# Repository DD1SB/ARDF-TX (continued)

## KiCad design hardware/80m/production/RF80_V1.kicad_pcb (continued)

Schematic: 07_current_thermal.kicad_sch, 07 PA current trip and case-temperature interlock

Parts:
C320: 10n; C_0603_1608Metric; MPN CC0603KRX7R9BB103
C321: 1n; C_0603_1608Metric; MPN CC0603JRNPO9BN102
C322, C323: 100n; C_0603_1608Metric; MPN CC0603KRX7R8BB104
R330: 0.05 ohm / 1% / 1W; R_2512_6332Metric; MPN WSL2512R0500FEA
R331, R332: 10; R_0603_1608Metric; MPN RC0603FR-0710RL
R333: 30k; R_0603_1608Metric; MPN RC0603FR-0730KL
R334, R335, R338, R340: 10k; R_0603_1608Metric; MPN RC0603FR-0710KL
R337: 60.4k; R_0603_1608Metric; MPN RC0603FR-0760K4L
R339: 1.3k; R_0603_1608Metric; MPN RC0603FR-071K3L
R348, R349: 0; R_0603_1608Metric; MPN RC0603JR-070RL; not fitted
TH301: 10k NTC / B25-50=3380; R_0603_1608Metric; MPN NCP18XH103F03RB
U313: INA180A1IDBVT; SOT-23-5; MPN INA180A1IDBVT
U314: LM393BIDR; SOIC-8_3.9x4.9mm_P1.27mm; MPN LM393BIDR

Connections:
GND: C321.2, C322.2, C323.2, R334.2, R338.2, R340.2, R348.2, R349.2, TH301.2, U313.2 (GND), U314.4 (V-); also elsewhere on the board
I_PA_FILTER: C321.1, R333.2, R334.1; also elsewhere on the board
I_PA_RAW: R333.1, U313.1
PACK_2S_REF: U314.2 (-); also elsewhere on the board
PA_GUARD_RAW: U314.7; also elsewhere on the board
SENSE_MINUS: C320.2, R332.2, U313.4 (-)
SENSE_PLUS: C320.1, R331.2, U313.3 (+)
TEMP_HOT_REF: R337.2, R338.1; also elsewhere on the board
TEMP_OPEN_REF: R339.2, R340.1, R348.1, U314.5 (+)
TEMP_SENSE: R335.2, R349.1, TH301.1, U314.6 (-); also elsewhere on the board
UV_POR_N: U314.1; also elsewhere on the board
V3V3: C322.1, C323.1, U313.5 (V+), U314.8 (V+); also elsewhere on the board
VPA_ISO: R330.1, R331.1; also elsewhere on the board
VPA_LOAD: R330.2, R332.1; also elsewhere on the board
VREF_TH: R335.1, R337.1, R339.1; also elsewhere on the board
V_PACK_SCALED: U314.3 (+); also elsewhere on the board

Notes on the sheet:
07 PA current trip and case-temperature interlock
Current trip nominal1.251A (20*0.05ohm=1V/A); targetfaultmute<=100us; dividergain0.25V/A;7.5ustau. Temperature window detects hot/short and detached/open sensor; nominalhot ~80C case. Values/thermal contact, comparator tolerance, filtering and trip latency are qualification gates.
M4A-V1: PRODUCTION-INTENT - NOT RELEASED / all physical gates NOT_RUN.

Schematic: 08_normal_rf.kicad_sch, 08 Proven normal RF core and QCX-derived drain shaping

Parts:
C401: 100n; C_0603_1608Metric; MPN CC0603KRX7R8BB104
C402: 1u; C_0805_2012Metric; MPN CC0805KKX7R9BB105
C403: 22u25; C_1210_3225Metric; MPN GRM32ER71E226KE15L
C404: 47u / 25V; CP_Elec_6.3x5.9; MPN 25SVPF47M
Q401, Q405: BSS138BK,215; SOT-23; MPN BSS138BK,215
Q402: IRF610PBF-BE3; Vishay_IRF610_TO220_StandardPTH; MPN IRF610PBF-BE3
Q403: BD140 / ST; ST_BD140_SOT32_StandardPTH; MPN BD140
Q404: DMN2056U-7; SOT-23; MPN DMN2056U-7
R401, R404: 10k; R_0603_1608Metric; MPN RC0603FR-0710KL
R402, R408: 47k; R_0603_1608Metric; MPN RC0603FR-0747KL
R403: 0; R_0603_1608Metric; MPN RC0603JR-070RL
R405: 1k; R_0603_1608Metric; MPN RC0603FR-071KL
R406: 100; R_2512_6332Metric; MPN CRCW2512100RFKEG
R407: 4.7k; R_0603_1608Metric; MPN RC0603FR-074K7L
R409: 100k; R_0603_1608Metric; MPN RC0603FR-07100KL
R410: 4.7; R_2512_6332Metric; MPN CRCW25124R70FKEG
T401: 9T + 9T bifilar / FT-50A-43; FT50A43_Inline_4Terminal; MPN Amidon FT-50A-43 + AWG24 enamel Cu
TP403: VPA_SHAPED; TestPoint_Pad_D1.0mm; MPN PCB pad / no purchased component
U401: LM5134BMF/NOPB; SOT-23-6; MPN LM5134BMF/NOPB

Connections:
CLK_PA: R408.1, U401.6 (IN); also elsewhere on the board
DRAIN_PA: Q402.2 (D), T401.2 (AB), T401.3 (SA)
GATE_DRV: R403.1, U401.3 (OUT)
GATE_PA: Q402.1 (G), R403.2, R404.1
GND: C401.2, C402.2, C404.2, Q402.3 (S), Q404.2 (S), Q405.2 (S), R402.2, R404.2, R407.2, R408.2, R409.2, U401.4 (VSS); also elsewhere on the board
KEY_DRAIN: Q404.3 (D), R406.2
KEY_TAIL: Q405.1 (G); also elsewhere on the board
PA_INB: Q401.3 (D), R401.2, U401.5 (INB)
PA_KEY: Q404.1 (G); also elsewhere on the board
PA_MUTE_MID: Q401.2 (S), Q405.3 (D), R409.1
PA_PERMIT: Q401.1 (G), R402.1; also elsewhere on the board
RF_RAW: T401.4 (SB); also elsewhere on the board
SHAPE_BASE: C403.2, Q403.1 (B), R405.2, R406.1
VDRV: C401.1, C402.1, C404.1, R401.1, R410.2, U401.1 (VDD); also elsewhere on the board
VPA_LOAD: Q403.3 (E), R405.1, R410.1; also elsewhere on the board
VPA_SHAPED: C403.1, Q403.2 (C), R407.1, T401.1 (AA), TP403.1; also elsewhere on the board

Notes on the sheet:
08 Proven normal RF core and QCX-derived drain shaping
RF core adapted from OpenARDF SignalSlinger HW3.5 (MIT); shaper principle from QCX/W6JL. Keep clock running during graceful key tail; INB immediately mutes on fault. This is NOT the VHF AM modulator.
No PA/drain reservoir after shaper. Driver reservoir is upstream. 9+9 series autotransformer: effective voltage step2:1, load~12.5ohm beforefilter. Transformer drawing is coupled coils; center join is external and explicit. All components on this sheet DNP on Fox-only. No watt-to-Fox RF switching.
M4A-V1: PRODUCTION-INTENT - NOT RELEASED / all physical gates NOT_RUN.

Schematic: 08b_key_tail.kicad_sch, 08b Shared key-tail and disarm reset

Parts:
C451: 100n; C_0603_1608Metric; MPN CC0603KRX7R8BB104
D451: BAT54WS-7-F; D_SOD-323; MPN BAT54WS-7-F
Q406: BSS138BK,215; SOT-23; MPN BSS138BK,215
R451: 1k; R_0603_1608Metric; MPN RC0603FR-071KL
R452: 330k; R_0603_1608Metric; MPN RC0603FR-07330KL
R453: 100; R_0603_1608Metric; MPN RC0603FR-07100RL

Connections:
CW_KEY: R451.1; also elsewhere on the board
GND: C451.2, Q406.2 (S), R452.2; also elsewhere on the board
KEY_TAIL_C: C451.1, D451.1 (K), R452.1, R453.1; also elsewhere on the board
KEY_TAIL_RESET_D: Q406.3 (D), R453.2
KEY_TAIL_SRC: D451.2 (A), R451.2
NOT_ARMED: Q406.1 (G); also elsewhere on the board

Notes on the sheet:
08b Shared key-tail and disarm reset
Path permission alone must not startRF during drain-integrator charging. Normal series INB sink needsPA_PERMIT andKEY_TAIL; FoxRFmute also requiresFOX_PERMIT andKEY_TAIL. Tail usesraw CW_KEY; disarm clampsmemorybelowSchmittlow. KEYhighcannotarm; capturedpath+withdrawaltrippreventsRFtransfer.
RCtailtau33ms; actualholddependsdiodedrop/HC14hysteresis. Benchqualify10-80mshold, longerthanthe3-8msRFdecay. ShorterfallcanclipRF; excessiveholdraisesidle/leakage. ARMlow>=20ms clearsmemory. Afterarming wait>=250msbeforefirstkey, thenverifysettleddrain. A fault bypassesgracefuldecay: PApermission/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
M4A-V1: PRODUCTION-INTENT - NOT RELEASED / all physical gates NOT_RUN.

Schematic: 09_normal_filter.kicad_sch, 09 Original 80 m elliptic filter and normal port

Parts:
C410: 470n; C_1206_3216Metric; MPN C3216X7R2A474K160AB
C411, C415: 1000p; C_0805_2012Metric; MPN C0805C102J1GACTU
C412, C416: 100p; C_0805_2012Metric; MPN C0805C101J1GACTU
C413: 1800p; C_0805_2012Metric; MPN C0805C182J1GACTU
C414: 91p; C_0805_2012Metric; MPN C0805C910J1GACTU
J401: NORMAL 50ohm reference; Phoenix_1727010_StandardPTH; MPN 1727010
L410, L411: 2.7 uH / 20T T60-2; T60_2_20T; MPN Micrometals T60-2 + AWG24 Cu
TP414: GND; TestPoint_Pad_D1.0mm; MPN PCB pad / no purchased component

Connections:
GND: C411.2, C412.2, C413.2, C415.2, C416.2, J401.2, TP414.1; also elsewhere on the board
LPF_N1: C410.2, C411.1, C412.1, L410.1
LPF_N2: C413.1, C414.1, L410.2, L411.1
RF_NORMAL: C414.2, C415.1, C416.1, J401.1, L411.2
RF_RAW: C410.1; also elsewhere on the board

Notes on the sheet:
09 Original 80 m elliptic filter and normal port
Retain SignalSlinger 80m values/topology: series470nF, two2.7uH, 1100/1800/1100pF,91pF acrosssecondcoil. Split1100pF into1000+100pF for obtainable capacitors. Coil recipe is mandatory; no generic power inductors.
Reference50ohm power: J401, calibrated adapter+dummyload. No antenna gain/ERP conversion on80m. Long antenna matcher remains separate: measured verticalwire+defined counterpoise, L-match/variometer. Normal match START range15-50uH fromDF1FO; exacttap/cap values requireinstalledimpedance. A screwter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
M4A-V1: PRODUCTION-INTENT - NOT RELEASED / all physical gates NOT_RUN.

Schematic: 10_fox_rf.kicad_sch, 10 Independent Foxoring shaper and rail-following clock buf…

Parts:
C501: 1u; C_0805_2012Metric; MPN CC0805KKX7R9BB105
C502: 100n; C_0603_1608Metric; MPN CC0603KRX7R8BB104
D501: BAT54WS-7-F; D_SOD-323; MPN BAT54WS-7-F
Q501: MMBT3906,215; SOT-23; MPN MMBT3906,215
Q502: BSS138BK,215; SOT-23; MPN BSS138BK,215
Q503, Q504: MMBT3904,215; SOT-23; MPN MMBT3904,215
R501: 27; R_2512_6332Metric; MPN RC2512FR-0727RL
R502, R504: 1k; R_0603_1608Metric; MPN RC0603FR-071KL
R503: 1.5k; R_0603_1608Metric; MPN RC0603FR-071K5L
R505, R508, R509: 10k; R_0603_1608Metric; MPN RC0603FR-0710KL
R506: 100k; R_0603_1608Metric; MPN RC0603FR-07100KL
R507: 470; R_0603_1608Metric; MPN RC0603FR-07470RL
TP501: VFOX; TestPoint_Pad_D1.0mm; MPN PCB pad / no purchased component
U501: SN74AC00DR; SOIC-14_3.9x8.7mm_P1.27mm; MPN SN74AC00DR

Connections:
CLK_FOX: R505.1; also elsewhere on the board
FOX_BASE: C501.2, Q501.1 (B), R502.2, R503.1
FOX_CLK: D501.1 (K), Q503.3 (C), R507.2, U501.1, U501.4, U501.9
FOX_CLK_B: D501.2 (A), Q503.1 (B), R505.2, R506.1
FOX_FEED: Q501.2 (E), R501.2, R502.1
FOX_GATE1: U501.3; also elsewhere on the board
FOX_GATE2: U501.6; also elsewhere on the board
FOX_GATE3: U501.8; also elsewhere on the board
FOX_GATE_EN: Q504.3 (C), R509.2, U501.2, U501.5, U501.10
FOX_KEY: Q502.1 (G); also elsewhere on the board
FOX_KEY_D: Q502.3 (D), R503.2
FOX_MUTE: R508.1; also elsewhere on the board
FOX_MUTE_B: Q504.1 (B), R508.2
GND: C502.2, Q502.2 (S), Q503.2 (E), Q504.2 (E), R504.2, R506.2, U501.7 (GND), U501.12, U501.13; also elsewhere on the board
V3V3: R501.1; also elsewhere on the board
VFOX: C501.1, C502.1, Q501.3 (C), R504.1, R507.1, R509.1, TP501.1, U501.14 (VCC)

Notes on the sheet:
10 Independent Foxoring shaper and rail-following clock buffer
TinyFox three-gate mechanism with stronger SN74AC00DR; new rail-following NPN input + QCX-style low-current envelope. No electrical RF connection to RF_RAW/RF_NORMAL. Nominal10mW is calibrated at separate J502, not inferred.
M4A-V1: PRODUCTION-INTENT - NOT RELEASED / all physical gates NOT_RUN.

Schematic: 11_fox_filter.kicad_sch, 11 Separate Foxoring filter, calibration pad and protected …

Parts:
C510: 470n; C_1206_3216Metric; MPN C3216X7R2A474K160AB
C511, C515: 1000p; C_0805_2012Metric; MPN C0805C102J1GACTU
C512, C516: 100p; C_0805_2012Metric; MPN C0805C101J1GACTU
C513: 1800p; C_0805_2012Metric; MPN C0805C182J1GACTU
C514: 91p; C_0805_2012Metric; MPN C0805C910J1GACTU
C517: 10n; C_0603_1608Metric; MPN CC0603KRX7R9BB103
J502: FOX ONLY / compact; JST_XH_B3B_StandardPTH; MPN B3B-XH-A(LF)(SN)
L510, L511: 2.7uH +/-5%; 78F_Axial; MPN 78F2R7J-RC
R510, R511, R512: 22; R_0603_1608Metric; MPN RC0603FR-0722RL
R513, R515: 750; R_0603_1608Metric; MPN RC0603FR-07750RL
R514: 6.8; R_0603_1608Metric; MPN RC0603FR-076R8L
R516: 10k; R_0603_1608Metric; MPN RC0603FR-0710KL
TP513: GND; TestPoint_Pad_D1.0mm; MPN PCB pad / no purchased component

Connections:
FOX_GATE1: R510.1; also elsewhere on the board
FOX_GATE2: R511.1; also elsewhere on the board
FOX_GATE3: R512.1; also elsewhere on the board
FOX_ID: C517.1, J502.3, R516.2; also elsewhere on the board
FOX_LPF1: C510.2, C511.1, C512.1, L510.1
FOX_LPF2: C513.1, C514.1, L510.2, L511.1
FOX_PAD_IN: C514.2, C515.1, C516.1, L511.2, R513.1, R514.1
FOX_SUM: C510.1, R510.2, R511.2, R512.2
GND: C511.2, C512.2, C513.2, C515.2, C516.2, C517.2, J502.2, R513.2, R515.2, TP513.1; also elsewhere on the board
RF_FOX: J502.1, R514.2, R515.1
V3V3: R516.1; also elsewhere on the board

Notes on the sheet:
11 Separate Foxoring filter, calibration pad and protected compact port
J502 reference plane: pin1 RF/pin2 definedreturn; use shorttwistedpair coaxadapter sharedfixture. Compactaccessory: ~30 cmradiator+definedcompactreturn; tune independentloading/couplingcartridge. StartingTinyFoxreference100uH plus1.6-15pF; effectiveC5-15pF mayrequire134-402uH. Exact30cm geometry/ta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
M4A-V1: PRODUCTION-INTENT - NOT RELEASED / all physical gates NOT_RUN.

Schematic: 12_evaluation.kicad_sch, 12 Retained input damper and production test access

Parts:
C350: 100u / 35V; CP_Radial_D8.0mm_P3.50mm; MPN EEUFR1V101
C405: 100n / 50V; C_0805_2012Metric; MPN GRM21BR71H104KA01L
R350: 1.5 ohm / 1W; R_2512_6332Metric; MPN CRCW25121R50FKEG
TP703: VPA; Probe_Pad_0p8; MPN PCB copper
TP706: VDRV; Probe_Pad_0p8; MPN PCB copper
TP716: ARMED; Probe_Pad_0p8; MPN PCB copper
TP717: RESET_N; Probe_Pad_0p8; MPN PCB copper
TP721: LEASE_OK; Probe_Pad_0p8; MPN PCB copper
TP723: PA_GUARD_RAW; Probe_Pad_0p8; MPN PCB copper

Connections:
ARMED: TP716.1; also elsewhere on the board
GND: C350.2, C405.2; also elsewhere on the board
LEASE_OK: TP721.1; also elsewhere on the board
PA_GUARD_RAW: TP723.1; also elsewhere on the board
RESET_N: TP717.1; also elsewhere on the board
VDRV: TP706.1; also elsewhere on the board
VIN_PA: C350.1, R350.2; also elsewhere on the board
VIN_PACK: R350.1; also elsewhere on the board
VPA: TP703.1; also elsewhere on the board
VPA_SHAPED: C405.1; also elsewhere on the board

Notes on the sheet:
12 Production test access input damper and low-capacitance probe access
M3B-E2: bounded12.0-16.8V protected4S only; first bring-up uses a CURRENT-LIMITED LAB SUPPLY. R350/C350 damp cable L<=10uH; pack sense remains ahead of R350. TVS is NOT an18V clamp. No driver fitted until power-only OV withdrawal test proves VDRV<=12.6V. No physical tests performed.
Population stages are assembly instructions, not bypasses of hardware interlocks. TH301 electrical sensor is remotely bonded to insulated PA case via test pads; do not fit a second NTC in parallel. R403 zero-ohm can be removed to isolate the gate driver during dummy-load tests. Do not inject28V int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
M4A-V1: PRODUCTION-INTENT - NOT RELEASED / all physical gates NOT_RUN.

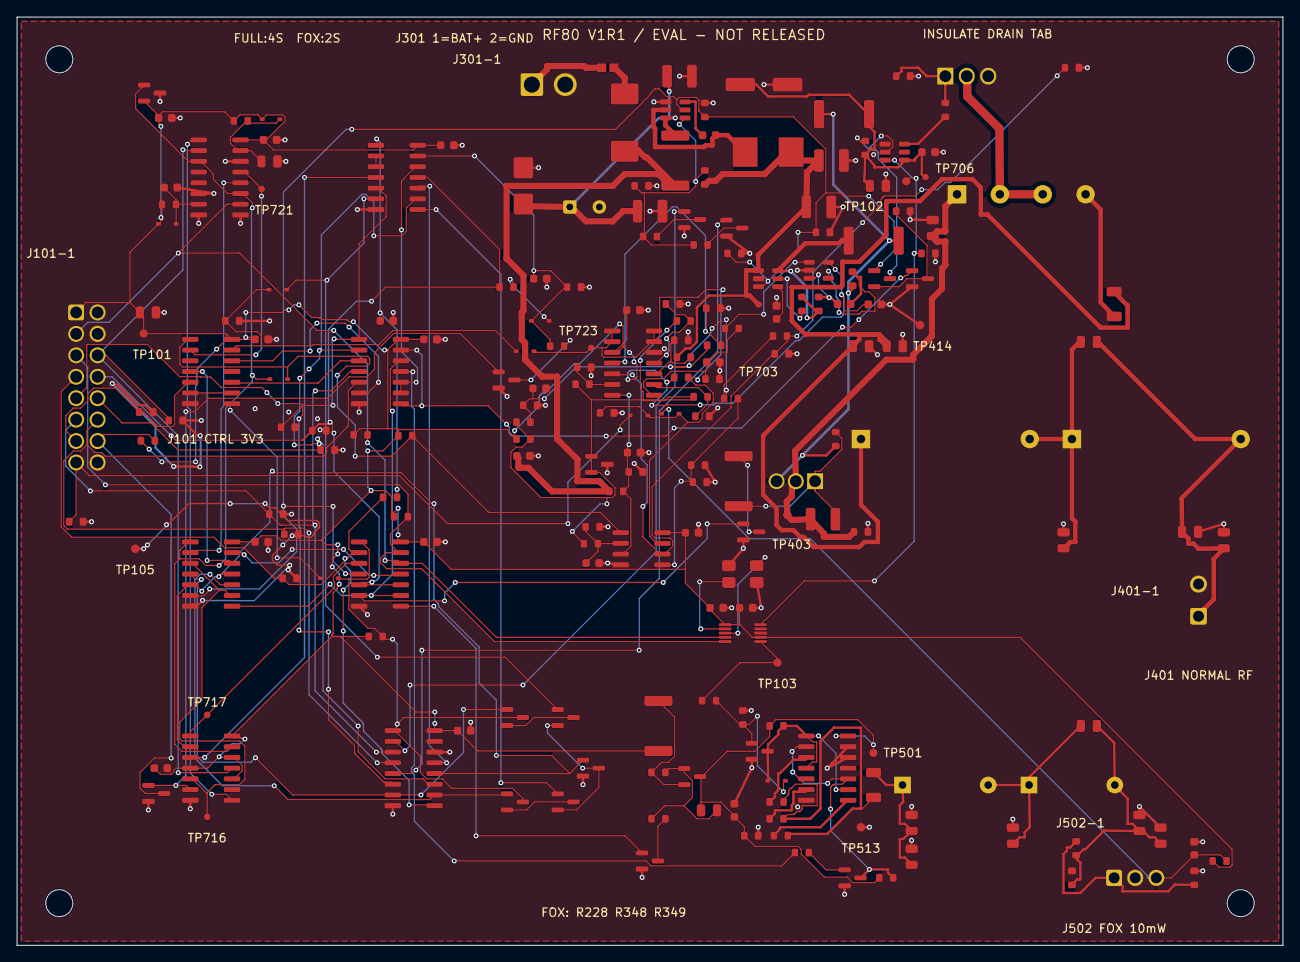
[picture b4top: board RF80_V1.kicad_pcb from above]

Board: 2 copper layers, 150.0 x 110.0 mm, 217 parts (0 on the bottom side), 120 nets.

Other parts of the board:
H1, H2, H3, H4: MountingHole_3.2mm_M3

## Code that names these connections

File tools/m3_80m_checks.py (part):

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    }
    for ref,pinsmap in needed.items():assert parts[ref]['pins']==pinsmap,(ref,parts[ref]['pins'])
    assert parts['Q403']['mpn']=='BD140'
    assert parts['Q401']['pins']=={'1':'PA_PERMIT','2':'PA_MUTE_MID','3':'PA_INB'}
    assert parts['Q405']['pins']=={'1':'KEY_TAIL','2':'GND','3':'PA_MUTE_MID'}
    assert parts['Q406']['pins']=={'1':'NOT_ARMED','2':'GND','3':'KEY_TAIL_RESET_D'}
    assert parts['U203']['pins']['13']=='KEY_TAIL_C' and parts['U203']['pins']['12']=='KEY_TAIL_N'
    assert parts['U212']['pins']['8']=='KEY_TAIL'
    assert parts['U212']['pins']['12']=='FOX_PERMIT' and parts['U212']['pins']['13']=='KEY_TAIL' and parts['U212']['pins']['11']=='FOX_MUTE'
    assert parts['R451']['pins']['1']=='CW_KEY'
    assert parts['U223']['pins']['1']=='RESET_N' and parts['U223']['pins']['2']=='ARM_ACCEPT' and parts['U223']['pins']['3']=='ARM_CLK' and parts['U223']['pins']['4']=='V3V3'
    assert parts['U202']['pins']['6']=='GND' and parts['U202']['pins']['14']=='GND'
    assert parts['D201']['pins']=={'1':'V3V3','2':'LEASE_RC'} and parts['D202']['pins']=={'1':'V3V3','2':'BUS_RC'}
    for ref in ('R451','D451','R452','C451','R453','Q406'):
        assert parts[ref]['population']=='BOTH'
    assert parts['D501']['mpn']=='BAT54WS-7-F'
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    for p in parts.values():
        if p['group']=='fox' or p['ref']=='J502':
            assert not forbidden.intersection(p['pins'].values()),p['ref']
    assert parts['U501']['pins']['14']=='VFOX'
    for pin in ('2','5','10'):assert parts['U501']['pins'][pin]=='FOX_GATE_EN'
    for ref in ('R510','R511','R512'):assert parts[ref]['pins']['2']=='FOX_SUM'
    # Pad and transmission-zero positions are different requirements from generic LPFs.
    assert set(parts['C414']['pins'].values())=={'LPF_N2','RF_NORMAL'}
    assert set(parts['C514']['pins'].values())=={'FOX_LPF2','FOX_PAD_IN'}
    assert parts['R501']['value']=='27'
    assert parts['R501']['footprint']=='Resistor_SMD:R_2512_6332Metric'
    assert parts['Q504']['pins']['3']=='FOX_GATE_EN'

    footprints=0
    for p in parts.values():
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
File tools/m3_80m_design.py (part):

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    s=d.sheet('01_source_interface','01 Controller interface and local source')
    s.text('One local Si5351; no MCU/RTC/UI on RF PCB. Shared 3.3 V stays powered during inhibited I2C setup.\nController wide-input regulator remains a proposal: evaluation fixture supplies bounded 3.3 V separately.',15,22)
    pins={'1':'V3V3','2':'GND','3':'SCL','4':'GND','5':'SDA','6':'LEASE','7':'ARM','8':'CW_KEY','9':'PA_REQ','10':'FOX_REQ','11':'PWR0','12':'PWR1','13':'MUTE_N','14':'FAULT_N','15':'PACK4_OK','16':'GND'}
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    r(s,'R349','0','TEMP_SENSE','GND',110,262,'FOX',note='Unused LM393 half input low in Fox-only; full DNP.')
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
    s=d.sheet('08_normal_rf','08 Proven normal RF core and QCX-derived drain shaping')
    s.text('RF core adapted from OpenARDF SignalSlinger HW3.5 (MIT); shaper principle from QCX/W6JL.\nKeep clock running during graceful key tail; INB immediately mutes on fault. This is NOT the VHF AM modulator.',15,23)
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    r(s,'R401','10k','VDRV','PA_INB',180,65,'NORMAL','normal_driver');fet(s,'Q401','PA_PERMIT','PA_INB','PA_MUTE_MID',245,65,'NORMAL','normal_driver');r(s,'R402','47k','PA_PERMIT','GND',315,65,'NORMAL','normal_driver')
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
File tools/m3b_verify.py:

#!/usr/bin/python3
"""Current PCB/netlist/R1 logic regression, package and artifact consistency."""
import csv,hashlib,json,os,sys
from pathlib import Path
from collections import Counter
import xml.etree.ElementTree as ET
import pcbnew as p
ROOT=Path(__file__).resolve().parents[1];HW=ROOT/'hardware/80m';REVISION=json.loads((HW/'RF80.electrical.json').read_text())['revision'];D=HW/'review'/REVISION;PREFIX='M3B_E2'if REVISION=='M3B-E2'else'M3B'
def main():
 m=json.loads((HW/'RF80.electrical.json').read_text());parts={x['ref']:x for x in m['parts']if not x['ref'].startswith('#')};b=p.LoadBoard(str(HW/'RF80.kicad_pcb'));fp={f.GetReference():f for f in b.GetFootprints()};xml=ET.parse(D/'RF80.xml')
 expected={}
 for n in xml.findall('./nets/net'):
  for nd in n.findall('node'):expected[(nd.attrib['ref'],nd.attrib['pin'])]=n.attrib['name'].removeprefix('/')
 assert set(parts)==set(fp)-{'H1','H2','H3','H4'}
 checked=0
 for r,f in fp.items():
  if r not in parts:continue
  assert str(f.GetFPID().GetLibNickname())+':'+str(f.GetFPID().GetLibItemName())==parts[r]['footprint'],(r,'FPID')
  for d in f.Pads():
   target=expected.get((r,d.GetNumber()),'');assert d.GetNetname()==target,(r,d.GetNumber(),d.GetNetname(),target);checked+=1
 for name in ('DRC','ERC'):
  j=json.loads((D/(name+'.json')).read_text());violations=j.get('violations',[v for s in j.get('sheets',[])for v in s.get('violations',[])]);assert not violations,(name,violations)
  if name=='DRC':assert not j['unconnected_items']and not j['schematic_parity']
 os.environ['RF80_NETLIST']=str(D/'RF80.xml')
 from m3a_r1_logic import verify
 lr=verify();assert lr['truth_cases']==256 and len(lr['state_scenarios'])==31 and len(lr['timing_corners'])==16
 (ROOT/('docs/'+PREFIX+'_LOGIC_RESULTS.json')).write_text(json.dumps(dict(evaluation_revision=REVISION,netlist=str((D/'RF80.xml').relative_to(ROOT)),retained_R1_contract=lr),indent=2)+'\n')
 tracks=[t for t in b.GetTracks()if not isinstance(t,p.PCB_VIA)];vias=[t for t in b.GetTracks()if isinstance(t,p.PCB_VIA)]
 assert all(t.GetWidth()>=p.FromMM(.15)for t in tracks)
 assert all(v.GetDrill()>=p.FromMM(.3)and v.GetWidth(p.F_Cu)>=p.FromMM(.6)for v in vias)
 for v in vias:
  for f in fp.values():
   for d in f.Pads():
    if d.GetAttribute()==p.PAD_ATTRIB_SMD:assert not d.HitTest(v.GetPosition()),('Via in SMD pad',f.GetReference(),d.GetNumber())
 # Independent manufacturer physical-pin maps, not symbol graphic order.
 maker={'U101':{'1':'V3V3','2':'XA','3':'XB','4':'SCL','5':'SDA','6':'CLK_FOX','7':'V3V3','8':'GND','10':'CLK_PA'},'U401':{'1':'VDRV','3':'GATE_DRV','4':'GND','5':'PA_INB','6':'CLK_PA'},'U301':{'1':'GND','2':'SW_PA','3':'VIN_PA','4':'FB_PA','5':'PA_PERMIT','6':'BOOT_PA'},'U302':{'1':'VPA','2':'GND','3':'PA_PERMIT','4':'CT_PA','5':'QOD_PA','6':'VPA_ISO'},'U313':{'1':'I_PA_RAW','2':'GND','3':'SENSE_PLUS','4':'SENSE_MINUS','5':'V3V3'},'Q402':{'1':'GATE_PA','2':'DRAIN_PA','3':'GND'},'Q403':{'1':'SHAPE_BASE','2':'VPA_SHAPED','3':'VPA_LOAD'},'U311':{'1':'VREF_2V5','2':'VREF_2V5','3':'GND'},'U202':{'13':'LEASE_OK','12':'BUS_HOLDOFF_N'},'U224':{'1':'HEALTH_N','9':'ARM'},'U501':{'7':'GND','14':'VFOX','3':'FOX_GATE1','6':'FOX_GATE2','8':'FOX_GATE3'},'J502':{'1':'RF_FOX','2':'GND','3':'FOX_ID'}}
 for ref,pinmap in maker.items():
  for pin,net in pinmap.items():assert expected[(ref,pin)]==net,(ref,pin,net)
 for q in parts.values():
  if q['group']=='fox':assert not set(q['pins'].values())&{'DRAIN_PA','GATE_PA','VPA_SHAPED','RF_NORMAL'}
 assert b.GetCopperLayerCount()==2
 assert all(abs(p.ToMM(q.GetDrillSize().x)-1.3)<.001 for q in fp['Q402'].Pads())
 assert all(abs(p.ToMM(q.GetDrillSize().x)-1.2)<.001 for q in fp['J101'].Pads())
 assert fp['F301'].GetFPID().GetLibItemName()=='Fuse_467_0603'
 assert len(list(b.Zones()))==2
 pads=[(r,f,parts[r])for r,f in fp.items()if r.startswith('TP')]
 with(D/'probe-map.csv').open('w')as out:
  w=csv.writer(out,lineterminator='\n');w.writerow(['reference','net','x_mm_absolute','y_mm_absolute','population','probe_caution'])
  for r,f,q in sorted(pads):w.writerow([r,q['pins']['1'],p.ToMM(f.GetPosition().x),p.ToMM(f.GetPosition().y),q['population'],'DRAIN: rated <=1pF active/differential'if q['pins']['1']=='DRAIN_PA'else 'Reset/clock: <=1pF active; local ground spring'])
 with(D/'population-map.csv').open('w')as out:
  w=csv.writer(out,lineterminator='\n');w.writerow(['reference','value','MPN','footprint','population','full_fit','fox_fit','x_mm_absolute','y_mm_absolute','rotation_deg'])
  for r,f in sorted(fp.items()):
   q=parts.get(r)
   if q:w.writerow([r,q['value'],q['mpn'],q['footprint'],q['population'],q['population']in('BOTH','NORMAL'),q['population']in('BOTH','FOX'),p.ToMM(f.GetPosition().x),p.ToMM(f.GetPosition().y),f.GetOrientationDegrees()])
 nets={}
 for n in ('GATE_DRV','GATE_PA','DRAIN_PA','VDRV','RF_NORMAL','RF_FOX','CLK_PA','CLK_FOX','SW_PA','VPA_ISO','VPA_LOAD'):
  ts=[t for t in tracks if t.GetNetname()==n];nets[n]=dict(track_length_mm=round(sum(p.ToMM(t.GetLength())for t in ts),3),widths_mm=sorted(set(round(p.ToMM(t.GetWidth()),3)for t in ts)),layers=sorted(set(b.GetLayerName(t.GetLayer())for t in ts)))
 models={}
 for f in fp.values():
  for model in f.Models():
   fn=model.m_Filename.replace('${KIPRJMOD}',str(HW)).replace('${KICAD10_3DMODEL_DIR}','/usr/share/kicad/3dmodels');assert Path(fn).exists(),fn;models[f.GetReference()]=model.m_Filename
 report=dict(date=m['date'],revision=REVISION,baseline_commit='55a5b3f',status='CAD AND IDEAL LOGIC CHECKS PASS; ALL PHYSICAL GATES NOT_RUN',manifest_refs=len(m['parts']),electrical_footprints=len(parts),mounting_holes=4,footprints=len(fp),physical_pad_memberships_checked=checked,manufacturer_pinmaps_checked=sorted(maker),test_pads=len(pads),track_segments=len(tracks),through_vias=len(vias),zones=2,board_mm=[210,160,1.6],copper_layers=2,track_width_histogram=dict(sorted(Counter(round(p.ToMM(t.GetWidth()),3)for t in tracks).items())),critical_net_geometry=nets,models_resolve=len(models),ERC_violations=0,DRC_violations=0,unrouted=0,schematic_parity=0,logic_truth_cases=256,state_scenarios=31,timing_corners=16,not_proved=['Physical propagation/reset recovery/metastability','Driver OV withdrawal timing and capacitor hot ESR','Cable/source transient envelope','RF power/efficiency/emissions/CW/thermal/antenna/isolation','Incoming exact component mechanical fit and stock'])
 (ROOT/('docs/'+PREFIX+'_CHECK_RESULTS.json')).write_text(json.dumps(report,indent=2)+'\n')
 print('PASS M3B:',checked,'pad net memberships;',len(fp),'footprints;',len(vias),'vias; ERC/DRC/parity/unrouted0; R1 256/31/16 retained')
if __name__=='__main__':main()

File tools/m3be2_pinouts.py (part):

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  if role=='CONTACT':continue
  if role in('INPUT','OUTPUT'):assert sp['electrical_type']==role.lower(),(ref,pin,'gate pin type')
  else:
   nm=sp['name'];aliases={'OUT':['','OUT'],'IN+':['+','IN+'],'IN-':['-','IN-'],'VS':['V+','VS'],'VCC':['VCC','VFOX']};assert nm in aliases.get(role,[role]),(ref,pin,role,nm)
 if ref=='Q403':
  assert a['rotation']==180 and a['pad_mm']=={'1':[160.56,69.0],'2':[158.28,69.0],'3':[156.0,69.0]},'Wrong ST installed orientation'
  # With +PCB-Y toward viewer and Z up, viewer-right is +PCB-X.
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 assert [m.m_Filename for m in q.Models()]==['${KIPRJMOD}/3dmodels/ST_BD140_envelope.wrl'],'Wrong ST envelope/orientation model'
 assert any(isinstance(t,pcb.PCB_TEXT)and t.GetText()=='ST BD140: DRAWING FACE TOWARD +Y'for t in b.GetDrawings()),'ST assembly face annotation disagrees'
 rejected=[]
 tests=[('Q403 XML pad1 emitter','Q403','netlist','1','VPA_LOAD'),('Q403 XML pad3 base','Q403','netlist','3','SHAPE_BASE'),('Q403 PCB pad1 emitter','Q403','pcb','1','VPA_LOAD'),('Q403 PCB pad3 base','Q403','pcb','3','SHAPE_BASE'),('TL431 old ground pin2','U311','pcb','2','GND')]
 for label,ref,key,pin,value in tests:
  bad=copy.deepcopy(a[ref]);bad[key][pin]=value
  try:check_one(ref,bad)
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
